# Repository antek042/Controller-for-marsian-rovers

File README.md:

# Controller-for-marsian-rovers

Controller for marsian rovers is a 4 key macropad with a 2 rotary encoders and OLED Dispaly. It uses KMK firmware.
It will be used soon in my mars rover project as a control pad!

## Features:
  - 3D printed case with big hole to see this beautiful PCB
  - 128x32 OLED Display
  - EC11 Rotary encoders for steering the rover and preying to don't hurt the rover
  - 4 keys for some future functions of rover

## CAD Model
Everything fits together using 6 M3 Bolts. 4 for the case, 2 for the PCB. It was made in Fusion360.

## PCB
The controller PCB was made in KiCad.

Schematic

PCB

## Firmware Overview
This hackpad uses [KMK](https://github.com/KMKfw/kmk_firmware) firmware for everything. 
  - the rotary encoders acts like arrows in keyboard
  - 4 keys for now is only function keys for steering rover
  - the OLED in the future will present you some stats from rover!!!

## BOM
Here should be everything you need to make this hackpad

- 4x Cherry MX Switches
- 4x DSA Keycaps
- 4x M3×10 mm
- 2x M3x5 mm
- 6x M3x5x4 Heatset inserts
- 4x 1N4148 DO-35 Diodes.
- 1x 0.91" 128x32 OLED Display
- 2x EC11 Rotary Encoder
- 1x XIAO RP2040
- 1x Case (2 printed parts)

## Extra stuff
[Click here to get a free Claude AI subscription for a year](https://www.youtube.com/watch?v=dQw4w9WgXcQ&list=RDdQw4w9WgXcQ&start_radio=1)

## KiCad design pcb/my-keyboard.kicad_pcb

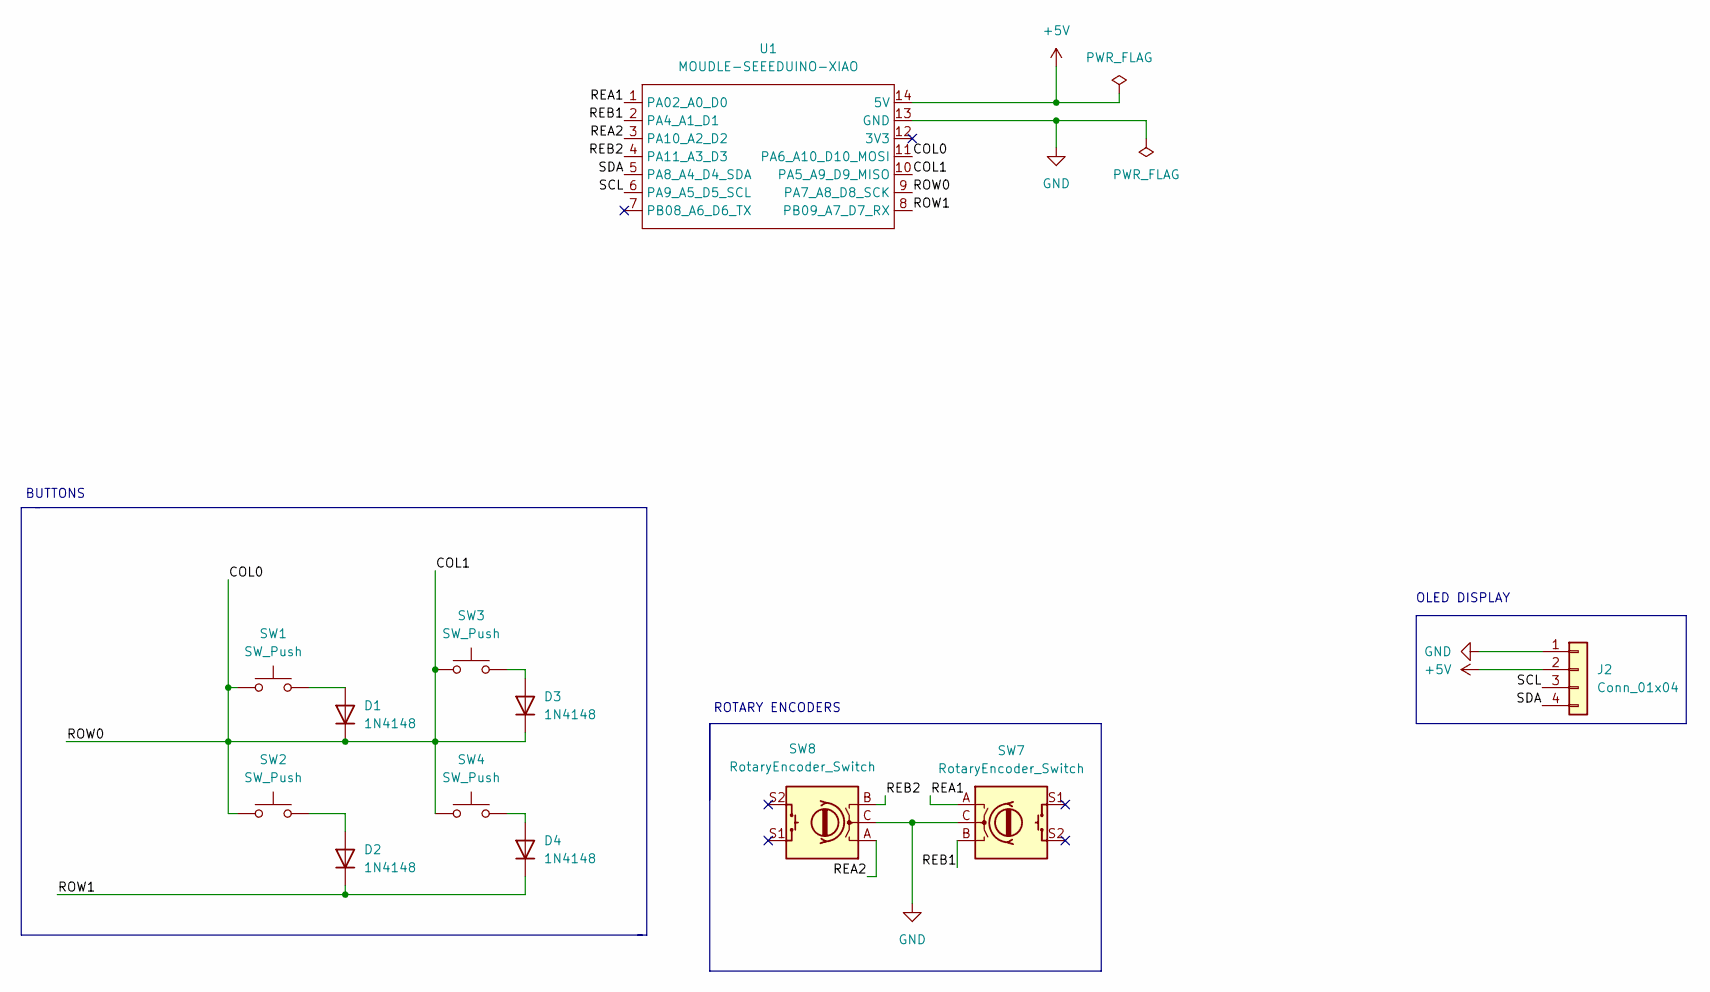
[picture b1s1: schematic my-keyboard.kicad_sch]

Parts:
D1, D2, D3, D4: 1N4148; D_DO-35_SOD27_P7.62mm_Horizontal
J2: Conn_01x04; SSD1306-0.91-OLED-4pin-128x32
SW1, SW2, SW3, SW4: SW_Push; SW_Cherry_MX_1.00u_PCB
SW7, SW8: RotaryEncoder_Switch; RotaryEncoder_Alps_EC11E-Switch_Vertical_H20mm
U1: MOUDLE-SEEEDUINO-XIAO; XIAO-Generic-Hybrid-14P-2.54-21X17.8MM

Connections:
+5V: J2.2, U1.14 (5V)
/COL0: D1.1 (K), D3.1 (K), SW1.1, SW2.1, SW3.1, SW4.1, U1.9 (PA7_A8_D8_SCK), U1.10 (PA5_A9_D9_MISO), U1.11 (PA6_A10_D10_MOSI)
/REA1: SW7.A, U1.1 (PA02_A0_D0)
/REA2: SW8.A, U1.3 (PA10_A2_D2)
/REB1: SW7.B, U1.2 (PA4_A1_D1)
/REB2: SW8.B, U1.4 (PA11_A3_D3)
/ROW1: D2.1 (K), D4.1 (K), U1.8 (PB09_A7_D7_RX)
/SCL: J2.3, U1.6 (PA9_A5_D5_SCL)
/SDA: J2.4, U1.5 (PA8_A4_D4_SDA)
GND: J2.1, SW7.C, SW8.C, U1.13 (GND)
unnamed: D1.2 (A), SW1.2
unnamed: D2.2 (A), SW2.2
unnamed: D3.2 (A), SW3.2
unnamed: D4.2 (A), SW4.2

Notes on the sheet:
BUTTONS
ROTARY ENCODERS
OLED DISPLAY

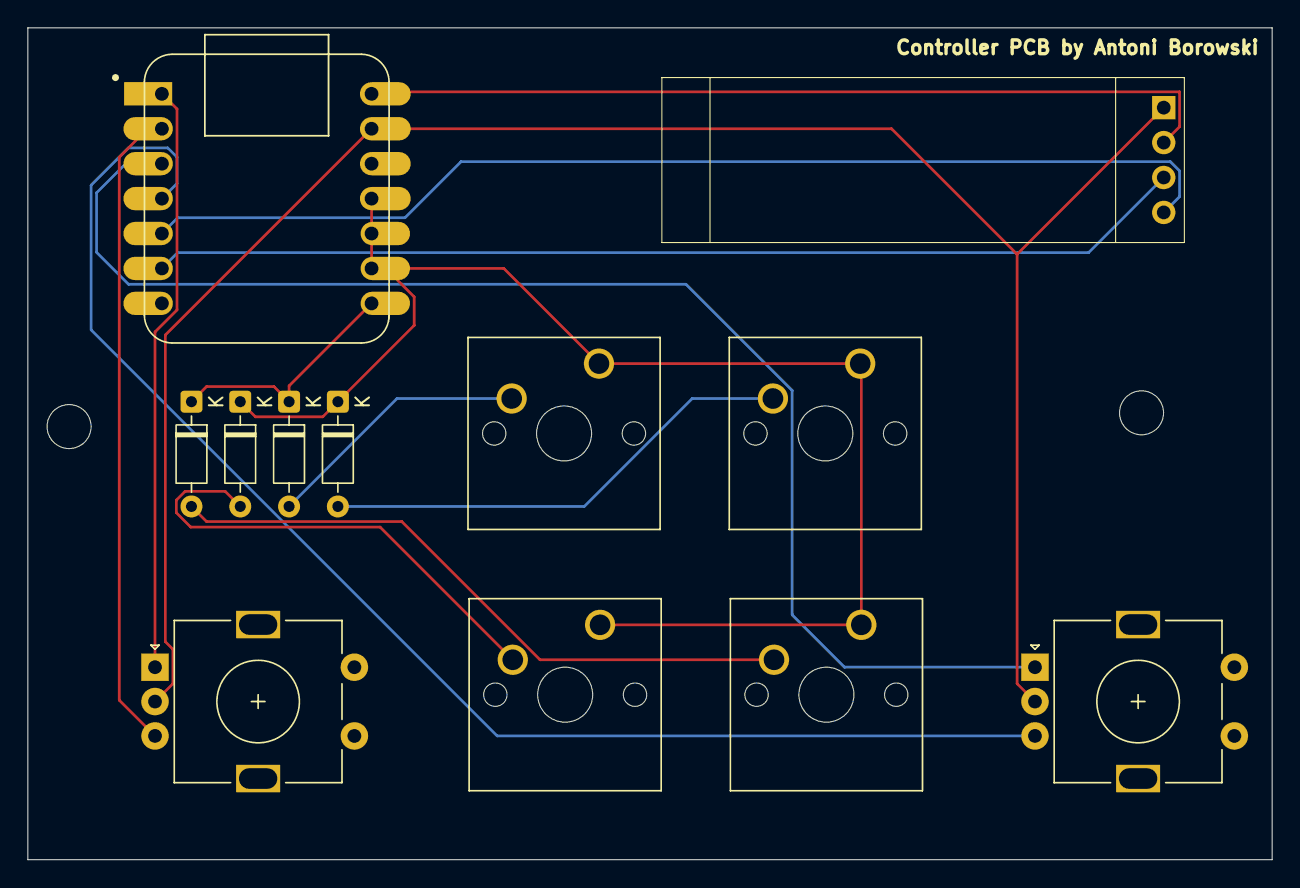
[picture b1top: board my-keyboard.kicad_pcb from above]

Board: 2 copper layers, 90.5 x 60.5 mm, 12 parts (0 on the bottom side), 14 nets.

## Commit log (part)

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2026-06-06 Add pcb for the controller
2026-06-06 New PCB and gerber files
2026-06-07 Add diodes for keyboard matrix
2026-06-08 Add basic firmware
